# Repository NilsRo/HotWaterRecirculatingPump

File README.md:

# Recirculation pump automated
How to optimize your water heating with an ESP32.

The project follows the ideas of https://github.com/MakeMagazinDE/Zirkulationspumpensteuerung and http://www.kabza.de/MyHome/CircPump/CirculationPump.php to control the hot water recirculation pump (Warmwasserzirkulationspumpe) via two temperature sensors comparing the warm water flow and return temperature. This saves electricity and thermal energy as the circulation will by done on request and not countinuously.

In the HT3 warm water diagram you see the period without warm water taking is flattend so the heater does heatup fewer.

## Featurelist
* Managing the pump via flow and return temperature
* MQTT publishing to get logging information
* MQTT subscription for your smart home and to use heater information like provided by https://github.com/norberts1/hometop_HT3
* Realtime clock for desinfection and logging
* SSD1306 OLED to view status information
* Guided setup to avoid storing WiFi password, etc. in the code
* 2 channel relay to add e.g. a magnetic vent later

## [Hardware](docs/schema.pdf)
* Wemos D1 Mini ESP32
* Standard Arduino/Raspberry 2-channel relay with optokoppler
* [BOM](docs/HotWaterRecirculatingPump.csv)
* STL for [case](docs/Warmwasserpumpe.stl) and [cover](docs/Warmwasserpumpe(2).stl)

## Mounting
The flow sensor have to be mounted 50cm away from the hot water reserviour. The return sensor near the end of the return pipe but not side by side to the reserviour. 

# Software
On first start the thing will open an Access Point named "Zirkulationspumpe" to provide the setup interface. The interface is still available after the device is connected so you can change everything later. But at first the firmware has to be uploaded. You can compile your own version or use the firmware provided in the releases.

1. Do the system configuration and set things name (hostname), AP password (if WiFi connection is lost) and WiFi credentials for your network.
2. MQTT configuration (optional)
   1. publish the following topics (folder structure can be changed):
      * "ww/ht/dhw_Tflow_measured": out temperature of the warm water
      * "ww/ht/dhw_Treturn": return temperature of the warm water circulation
      * "ww/ht/dhw_Tdelta": difference detected in the 5s time window
      * "ww/ht/Tint": system internal temperature
      * "ww/ht/dhw_pump_circulation": pump is running or not
      * "ww/ht/dhw_valve_opened": valve is currently open (true/false)
      * "ww/ht/dhw_valve_sec_opened": how many seconds the valve has been open
      * "ww/ht/dhw_valve_sec_to_refill": seconds until a refill was neccessary. Could be used for alerting purposes if there is a leakage.
      * "ww/ht/dhw_valve_pressure_avg": average system pressure value
      * "ww/ht/status": availability of the system is connected to mqtt broker (Online) or not (Offline)
      * "ww/ht/wifi": wifi related infos like signal quality
      * "ww/ht/sysinfo": status of the system showing the actual mode as Json
        * mode 
          * auto - automatic mode
          * manual - control the pump via the button. The 24h timer to clean the pipes is still running.
        * state
          * heater on - temperature is watched and pump is starting automatically or by MQTT triggers
          * heater off - pump can be started by MQTT triggers
          * desinfection - Desinfection is running, all triggers are blocked until the desinfection is finished by MQTT trigger
          * emergency - some sort of problem detected like with DS18B20. The pump will start by a timer regularly.
      * "ww/ht/info": system information as text
   2. subscribe to heater topics
      * heater status topic (e.g. ht3/hometop/ht/hc1_Tniveau): if the value is matched the system switches to automatic mode. If it is not matched the pump is off and reacts on desinfection and manual starts only.
      * external pump start topic (e.g. ht3/hometop/ht/dhw_pump_circulation):  The event is triggered if the message contains the value set in the configuration. The pump will swtched off if the desired return temperature is reached. Could be used to have a dump switch with HT3 and avoids buying a second IPM module for water pump (automatic mode should be disabled) or much better you can trigger the pump from your smart home or something more advanced.
      * thermal desinfection topic (e.g. ht3/hometop/ht/dhw_thermal_desinfection): if the value is matched the pump will switch on infinitly until another value is received on this topic. This can be used for desinfection topics. If desinfection is switched off the pump will still run until the necessary temperature is reached on the return pipe to guarantee the desinfection of the whole pipe.
3. NTP configuration to get RTC infos for logging (default is fine for german timezone)
4. Temperature configuration to map DS18B20 sensors detected
5. Define your return temperature to switch off when the water is gone through the whole circulation pipe.
6. button short press to swtich screen, button long press for testing the relay/pump.

## OLED infos

# Tips
* Increase the pumps flow to the maximum that the water goes through the pipes as fast as possible.
* Setup special schedules via a smart home (MQTT) if you like to have warm water on request (e.g. by phone) or at a specific time.
* second relay channel is actually unused - suggest how to use it if you need
* If you are using separate networks for IoT devices it is not possible to flash the device with ArduinoOTA as it using broadcast messages that are usually dropped in the firewall. For that setup you should use HTTP upload in the config page to upload the firmware.bin.

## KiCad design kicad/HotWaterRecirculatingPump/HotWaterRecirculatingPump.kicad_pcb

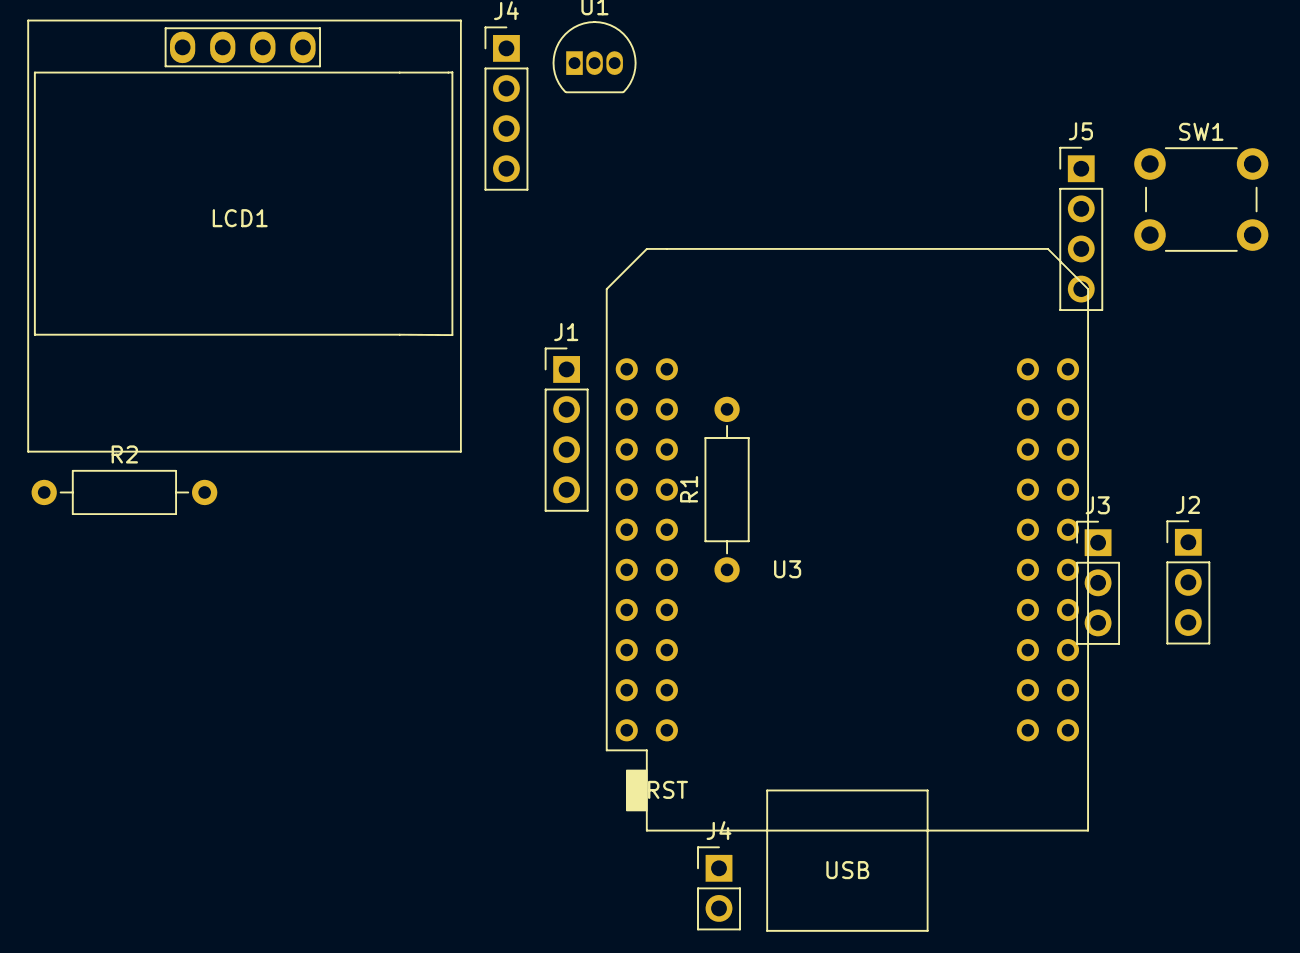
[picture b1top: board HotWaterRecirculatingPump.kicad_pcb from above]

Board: 2 copper layers, 12 parts (0 on the bottom side), 15 nets, no tracks yet.

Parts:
J1: Dual Relay; PinHeader_1x04_P2.54mm_Vertical
J2, J3: DS18B20; PinHeader_1x03_P2.54mm_Vertical
J4: SW_DISPLAY_PAGE; PinHeader_1x02_P2.54mm_Vertical
J4#2: BUTTON_LED; PinHeader_1x04_P2.54mm_Vertical
J5: DISPLAY I2C; PinHeader_1x04_P2.54mm_Vertical
LCD1: SSD1306; 128x64OLED
R1, R2: 1kOhm; R_Axial_DIN0207_L6.3mm_D2.5mm_P10.16mm_Horizontal
SW1: SW_WIFI_CONF; SW_PUSH_6mm_H4.3mm
U1: DS18B20; TO-92_Inline
U3: mini_esp32; ESP32_mini

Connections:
GND: J2.3, J3.3, U1.1 (GND)
unnamed: J1.1, U3.35 (VCC_(USB))
unnamed: J1.2, U3.31 (IO_16/D4)
unnamed: J1.3, U3.29 (IO_17/D3)
unnamed: J1.4, U3.33 (GND)
unnamed: J2.1, J3.1, LCD1.2 (VCC), R1.1, U1.3 (VDD), U3.16 (3V3)
unnamed: J2.2, J3.2, R1.2, U1.2 (DQ), U3.14 (IO_05/D8)
unnamed: J4#2.1, J4#2.3, LCD1.1 (GND), SW1.2, U3.22 (GND)
unnamed: J4#2.2, U3.8 (IO_18/D5)
unnamed: J4#2.4, R2.1
unnamed: LCD1.3 (SCL), U3.25 (IO_22/D1/SCL)
unnamed: LCD1.4 (SDA), U3.27 (IO_21/D2/SDA)
unnamed: R2.2, U3.10 (IO_19/D6)
unnamed: SW1.1, U3.12 (IO_23/D7)
unnamed: J4.1, J5.1

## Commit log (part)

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2022-10-12 first version
2022-10-12 Added diaplay pages, NTP Server, Last pumps page,
2022-10-13 Corrected display, added hystersis to check loop and avoided delay
2022-10-15 Corrected Button handling
2022-10-17 Display integration, Emergency Mode
2022-10-18 Display and DS18B20 handling
2022-10-18 Sensorerror in MQTT added
2022-10-19 Added new WiFi screens
2022-10-28 Corrected display page 2
2022-10-28 Added OTA Update HTTP Server
2022-10-28 WiFi Output power to maximum
2022-10-28 Update schema.pdf
    Added capacitors to schematics to avoid brownout
2022-10-28 Kicad, README, BOM, pictures
2022-10-28 Gitignore for Kicad
2022-10-28 Formatting, added manual pump switch
2022-10-29 Wifi scan working
2022-10-29 Wifi Networks showed in list -Display 6
2022-10-29 Display Refresh to 500ms, NTP only on connected network
2022-10-29 Removed Backupfiles
2022-10-29 Better Wifi Scan Display handling
2022-10-29 Small layout optimizations
2022-10-29 Better Config page, OTA
2022-10-29 Housekeeping
2022-10-29 better HTML Status output
2022-10-29 5 last pumpaction in HTML view
2022-10-29 Last Pump Actions corrected
2022-10-30 Array Length function, Pump First Call
2022-10-30 Corrected order of last pump actions
2022-10-30 Datatype convertion issue
2022-10-31 MQTT Subscription for heater status
2022-10-31 fixed heater status
2022-10-31 Fix HeaterStatus, MQTT optimization
2022-10-31 README
2022-10-31 Markdown
2022-10-31 images
2022-10-31 updated PDF
2022-11-01 Added external pump trigger
2022-11-01 fixed empty subscripton handling
2022-11-01 draw io diagram
2022-11-01 draw.io
2022-11-01 draw.io Atlas
2022-11-01 added MQTT thermal desinfection
2022-11-01 Formatting
2022-11-01 Deleted unnecessary WiFi code
2022-11-02 MQTT config bug, WiFi Workaround
2022-11-02 fix string compare MQTT
2022-11-02 MQTT QoS
2022-11-02 optimized pumpOff after activation
2022-11-06 Workaround for WiFi Settings with preferences
2022-11-11 Thermal desinfection, MQTT added to Status Page
2022-11-12 better layout in status page
2022-11-14 runtime days to 4 digits
2022-11-18 optimized statuspage
2022-11-18 the same
2023-01-20 Trigger Temp Diff included in config
2023-01-22 Chenged Disinfection timer to millis compare
2023-02-02 README typos
2023-02-10 Added language selector for OLED
2023-04-03 - MQTT Publish centralized - added topic path as parameter - Corrected date display in log
2023-04-03 Uptime published every 10 minutes
2023-04-07 MQTT correction, added more info to status page
2023-04-20 Added error codes for unexpected reset
2023-04-23 Optimized MQTT handling on reconnect Added Core Dump function
2023-04-23 MQTT init behavior changed
2023-04-24 Fixed thermal desinfection mqtt mode
2023-04-24 deleted unneccessary variable
2023-04-29 Added MQTT Status
2023-04-30 added emrgency to status
2023-05-03 - Status changed - Typos in status page - trigger handling fixed if heater is off
2023-05-04 Changed status output to Json
2023-05-04 Webpage type
2023-05-26 Added core dump download function
2023-05-26 Added deletion of core dump
2023-05-31 Backbutton on delete coredump page
2023-06-03 Local IP is never available on boot
2023-06-03 Display on for OTA
2023-06-03 Handled OTA better with Wifi Connected Events
2023-06-03 Some logging messages
2023-06-03 Added MQTT disconnect time
2023-06-15 Added exception decoder MQTT trigger will trigger pump everytime
2023-12-02 Corrected log output if settings are restored
2023-12-02 settings restore corrected (Ap Password)
2024-04-01 optimized mqttTopic sends if disconnected
2024-12-04 Better "healing" in case of a sensor error
2024-12-05 Read temp even if there is a sensor error
2024-12-16 - Added sensor info to mqtt - fixed assignment of sensors to function - status topic added - old status topic renamed to sysinfo
2024-12-18 Issue with last will of MQTT Client - broken connection
2024-12-18 Update ArduinoJson
2024-12-19 - Activated LastWill Topic - Updated ArduinoJson handling
2024-12-19 Added connection status to overview
2025-10-13 Activated second relay to control a valve via MQTT
2025-10-26 Added valve and tested behavior
2025-10-26 Added TempDiff Topic
2025-11-18 Valve Texts
2025-11-18 TempDelta Save
2025-11-18 Cleaned global variable init
2025-11-18 Added feature for automatic refill of heater system
2025-11-19 Added extended OTA environment
2025-11-19 Typo
2025-11-19 Pushed Dallas Lib to V4
2025-11-24 Added arduino-timer to avoid conflicts with interrupt based timers
2025-11-24 Corrected Serial log output
2025-11-25 Added average pressure Added new sysinfo format
2025-11-26 added regions
2025-11-26 Update MQTT interface to ImpulseMeter standard
2025-11-27 Refactored MQTT handling
2025-11-27 Correct OTA flash partition layout
2025-11-27 Corrected syslog Changed 10min to 1min timer for better pressure adoption
2025-11-27 Added HTML pressure vs pressure avg
2025-12-01 Store and send time between fillings
2025-12-01 Added pressure to display
2025-12-01 Sec to Refill topic Sysinfo JSON structure
2026-02-07 Added init fill to handle low pressure after reset
2026-02-12 Valve history, float compare correction
2026-02-12 Added initial fill flag to syslog
2026-04-09 Reduced calls to 1-Wire Bus
2026-04-09 Too long text for display
2026-04-16 Moved 1-Wire to CPU Thread 1
2026-05-02 Disabled EDF Coredump because of incompatibility to Arduino Framework
2026-05-02 Fix HexStr2Arr conversion length (overflow)
2026-05-02 - IDF bootloader to handle OTA partitions - watchdog for arduino loop - crash counter for partition switch
2026-05-05 Restructured plaform.io builds
2026-05-05 - changed logging to ESP_LOG - added syslog logging - changed button handling to OneButton library - hamonized manual mode between valve and pump
2026-05-05 Corrected OTA partition selection
2026-05-05 If manual mode is on never switch of display to recognize it
2026-05-05 new config version 7 flag
2026-05-05 Changed logging to direct UART access
2026-05-15 Automatic failover to backup partition after 10 panics
2026-05-16 Secured ArduinoOTA with local AP password
2026-05-17 Watchdog - 3 minutes timeout because of firmware update
2026-05-19 Added valve refill to README
2026-05-23 First verion of HA Autodiscovery
